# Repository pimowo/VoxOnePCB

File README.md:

# VoxOnePCB — VoxOne_M1

Repozytorium projektu płytki **VoxOne_M1** (KiCad 10.0.4). Oddzielone od firmware VoxOne/VoxOneBT.

## Dokumentacja

- [TODO.md](TODO.md) — **kanoniczny notatnik** zadań, zatwierdzonych wytycznych, blokad i historii.
- [AGENTS.md](AGENTS.md) — zasady pracy lokalnego Codexa.
- [docs/IMPORT_KICAD.md](docs/IMPORT_KICAD.md) — bezpieczne przeniesienie źródeł projektu na GitHub.

## Zatwierdzone wymagania PCB

- Laminat maksymalnie **100 × 100 mm**; cztery otwory M3.
- **2 warstwy miedzi**, ścieżki TOP i BOTTOM.
- **Wszystkie elementy montowane wyłącznie od góry (TOP)** — SMD i THT, moduły, goldpiny, zworki.
- MAIN po lewej, DAC w górnej prawej części, BT po prawej, RTC blisko środka, dolna strefa uporządkowanych złączy: **wytyczna koncepcyjna**, wymagająca mechanicznej kontroli.
- Moduły MAIN/BT/DAC/RTC wymienne.

## Stan projektu

Ostatnia importowana rewizja: **FOOTPRINT-2 + PCB-PREVIEW-1**. Według raportu Codexa: ERC 0 błędów i 0 ostrzeżeń; wstępne PCB 100 × 100 mm bez trasowania. **Rozmieszczenie PREVIEW-1 zostało odrzucone.** Nie tworzyć Gerberów ani nie trasować tej wersji. Geometrie trzech dużych modułów są referencyjne (PROVISIONAL), niepotwierdzone na fizycznych egzemplarzach.

**Źródła projektu KiCad i biblioteki są już opublikowane w repozytorium**, od bazowego commita [`8d90e6d`](https://github.com/pimowo/VoxOnePCB/commit/8d90e6df444f770a445944372fa62b5ebb39af9). W repo znajdują się pliki `.kicad_pro`, `.kicad_sch`, `.kicad_pcb`, projektowe biblioteki footprintów/symboli i wybrane modele 3D. Z publikacji wyłączono modele `YD-ESP32-S3.step` i `PCM5102-I2S.step` do dalszej weryfikacji praw. Po imporcie projekt otwarto w KiCad 3D, ale **należy ponownie wykonać ERC/DRC/netlist na czystym klonie**. Wersja jest PROVISIONAL i nie jest zatwierdzona do produkcji.

## Dostęp i prawa

Repozytorium jest **publiczne**. Nie publikować kluczy, haseł, danych prywatnych, ani obcych modeli 3D/bibliotek bez zgodnej licencji. **Licencja własnego projektu nie została jeszcze wybrana** — nie dodawać `LICENSE` automatycznie.

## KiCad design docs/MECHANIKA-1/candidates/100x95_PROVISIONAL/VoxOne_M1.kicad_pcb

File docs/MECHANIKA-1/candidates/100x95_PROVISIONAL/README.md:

# Kandydat analityczny 100×95 mm — PROVISIONAL

Otwórz `VoxOne_M1.kicad_pro` w tym katalogu. To niezależna kopia do analizy, nie zmiana głównego PCB. Schemat A2 i konfiguracja są bajtowo identyczne ze źródłem. Footprinty/symbole/modele są współdzielone przez ścieżki względne do głównego katalogu repozytorium; przenoś cały klon, nie sam ten podkatalog. Pełny model MAIN działa tylko lokalnie i nie jest publikowany. Nie ma pełnych brył BT/DAC/RTC/F101. Braki są jawne w podglądzie3D.

77 TOP,4M3,0tras/via/pours,ERC0/0,DRC173niepołączenia i0innych naruszeń. Nie jest to DRC PASS ani finalny layout. Wygoda złączy, tolerancje iZ są niepotwierdzone; patrz raporty dwa katalogi wyżej. Nie trasować ani nie produkować bez nowego polecenia użytkownika.

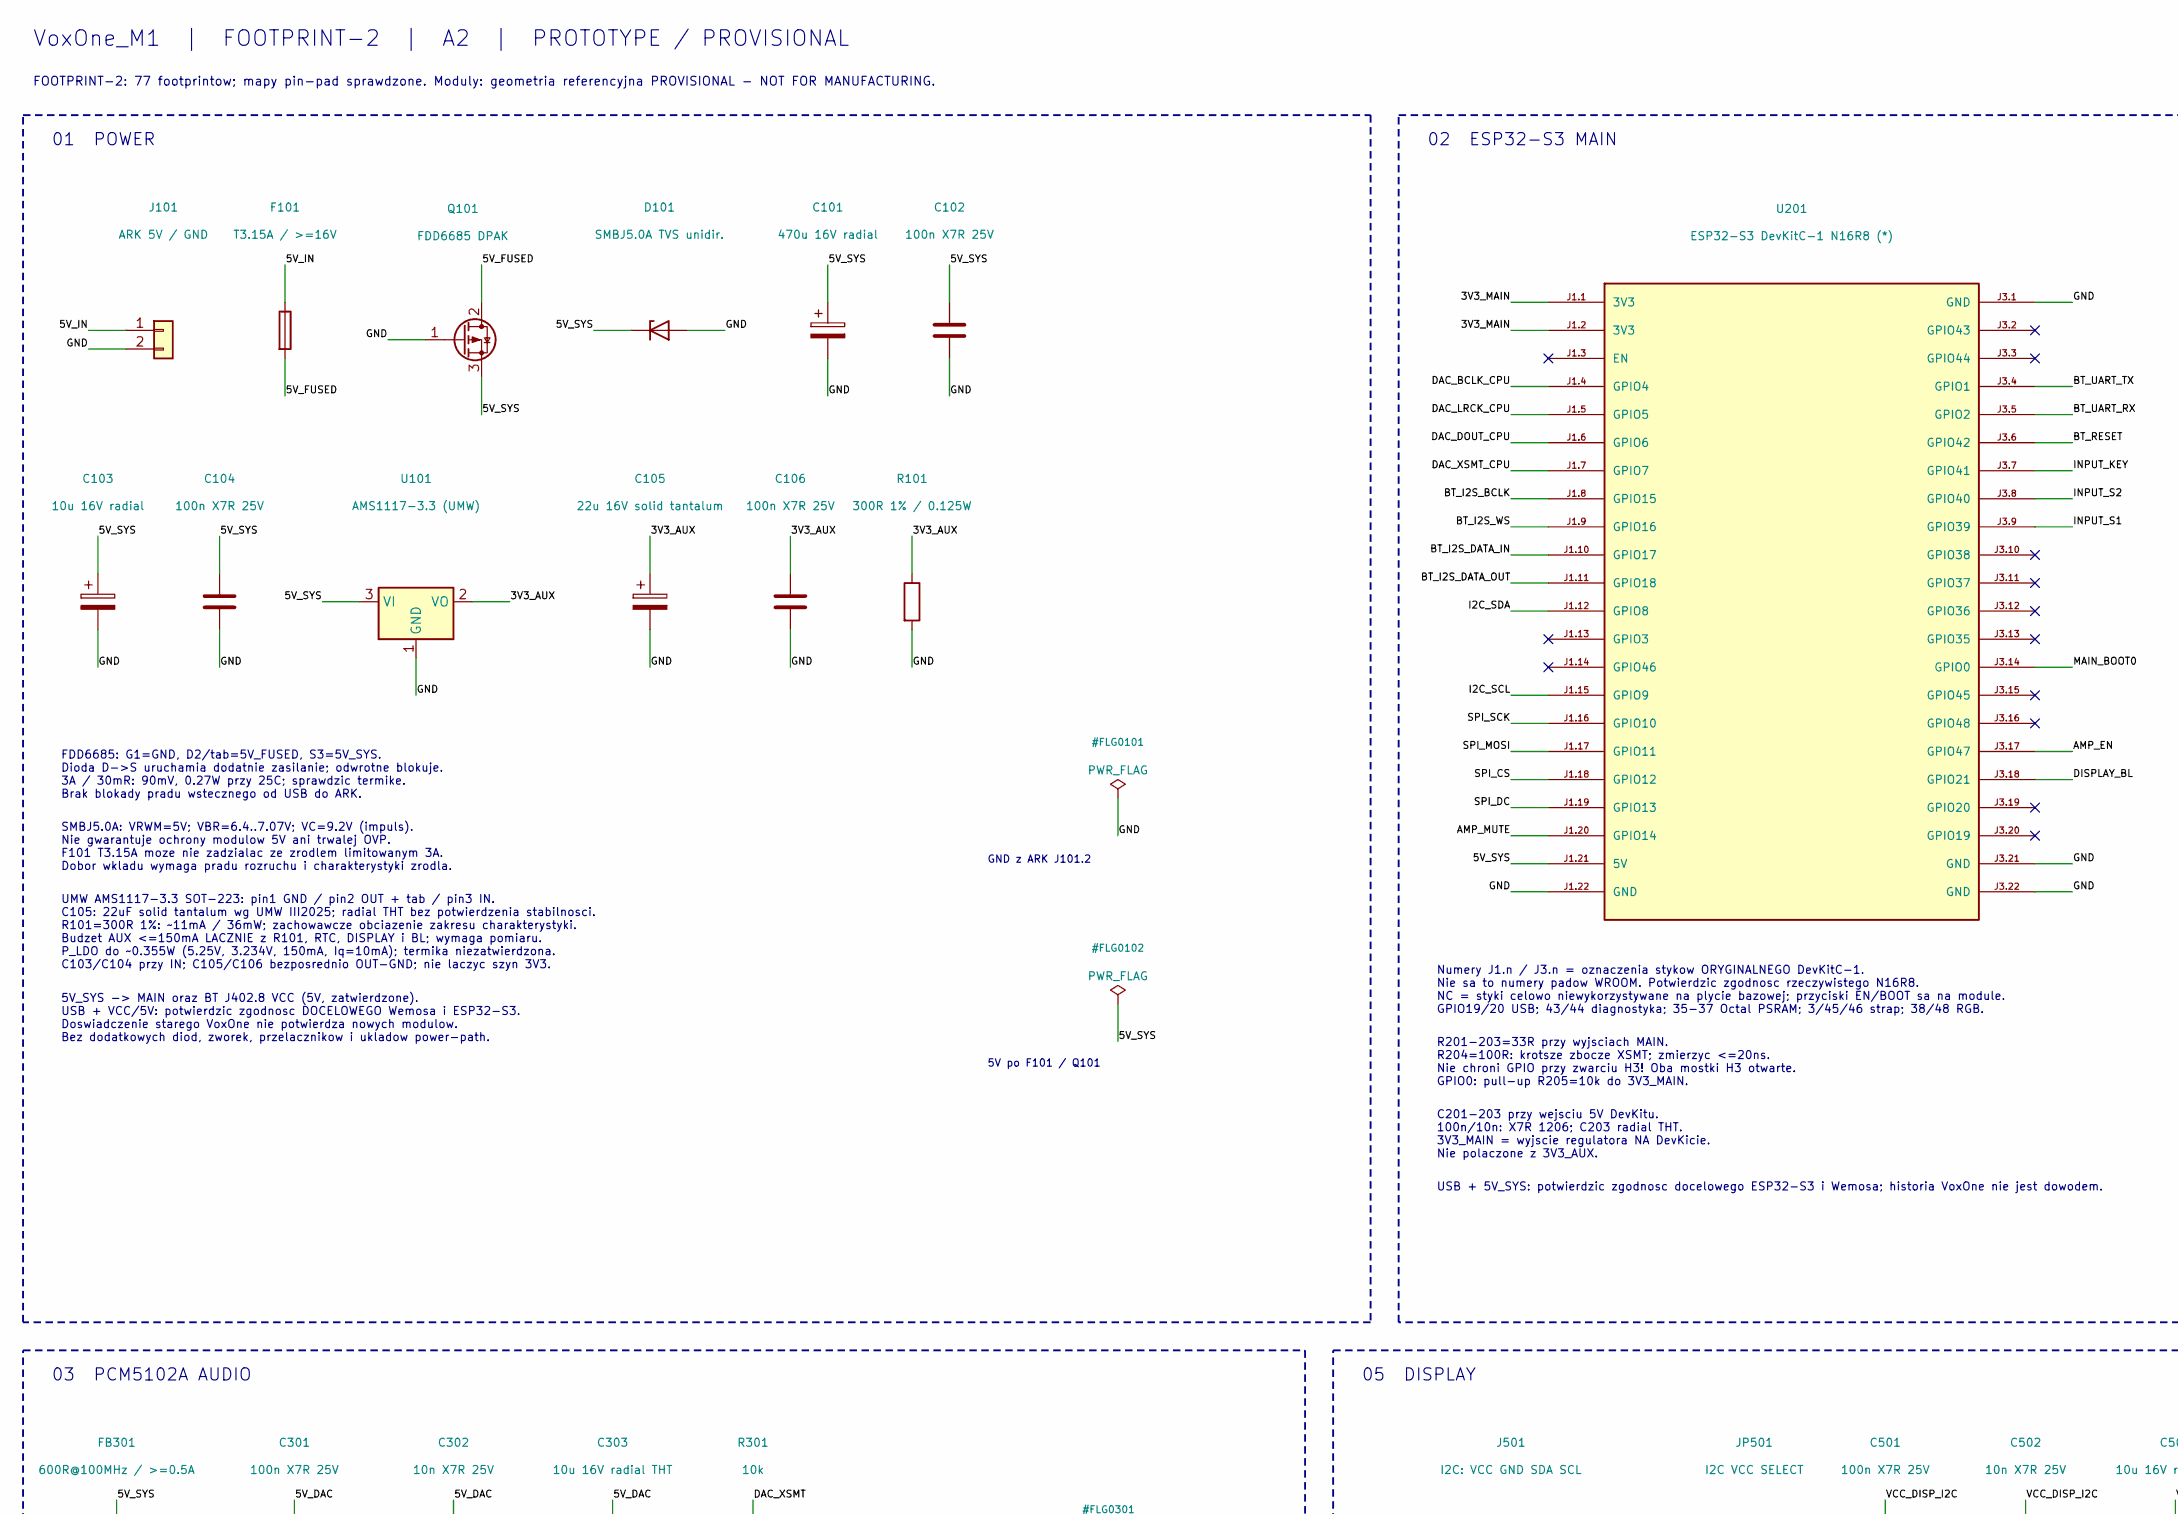
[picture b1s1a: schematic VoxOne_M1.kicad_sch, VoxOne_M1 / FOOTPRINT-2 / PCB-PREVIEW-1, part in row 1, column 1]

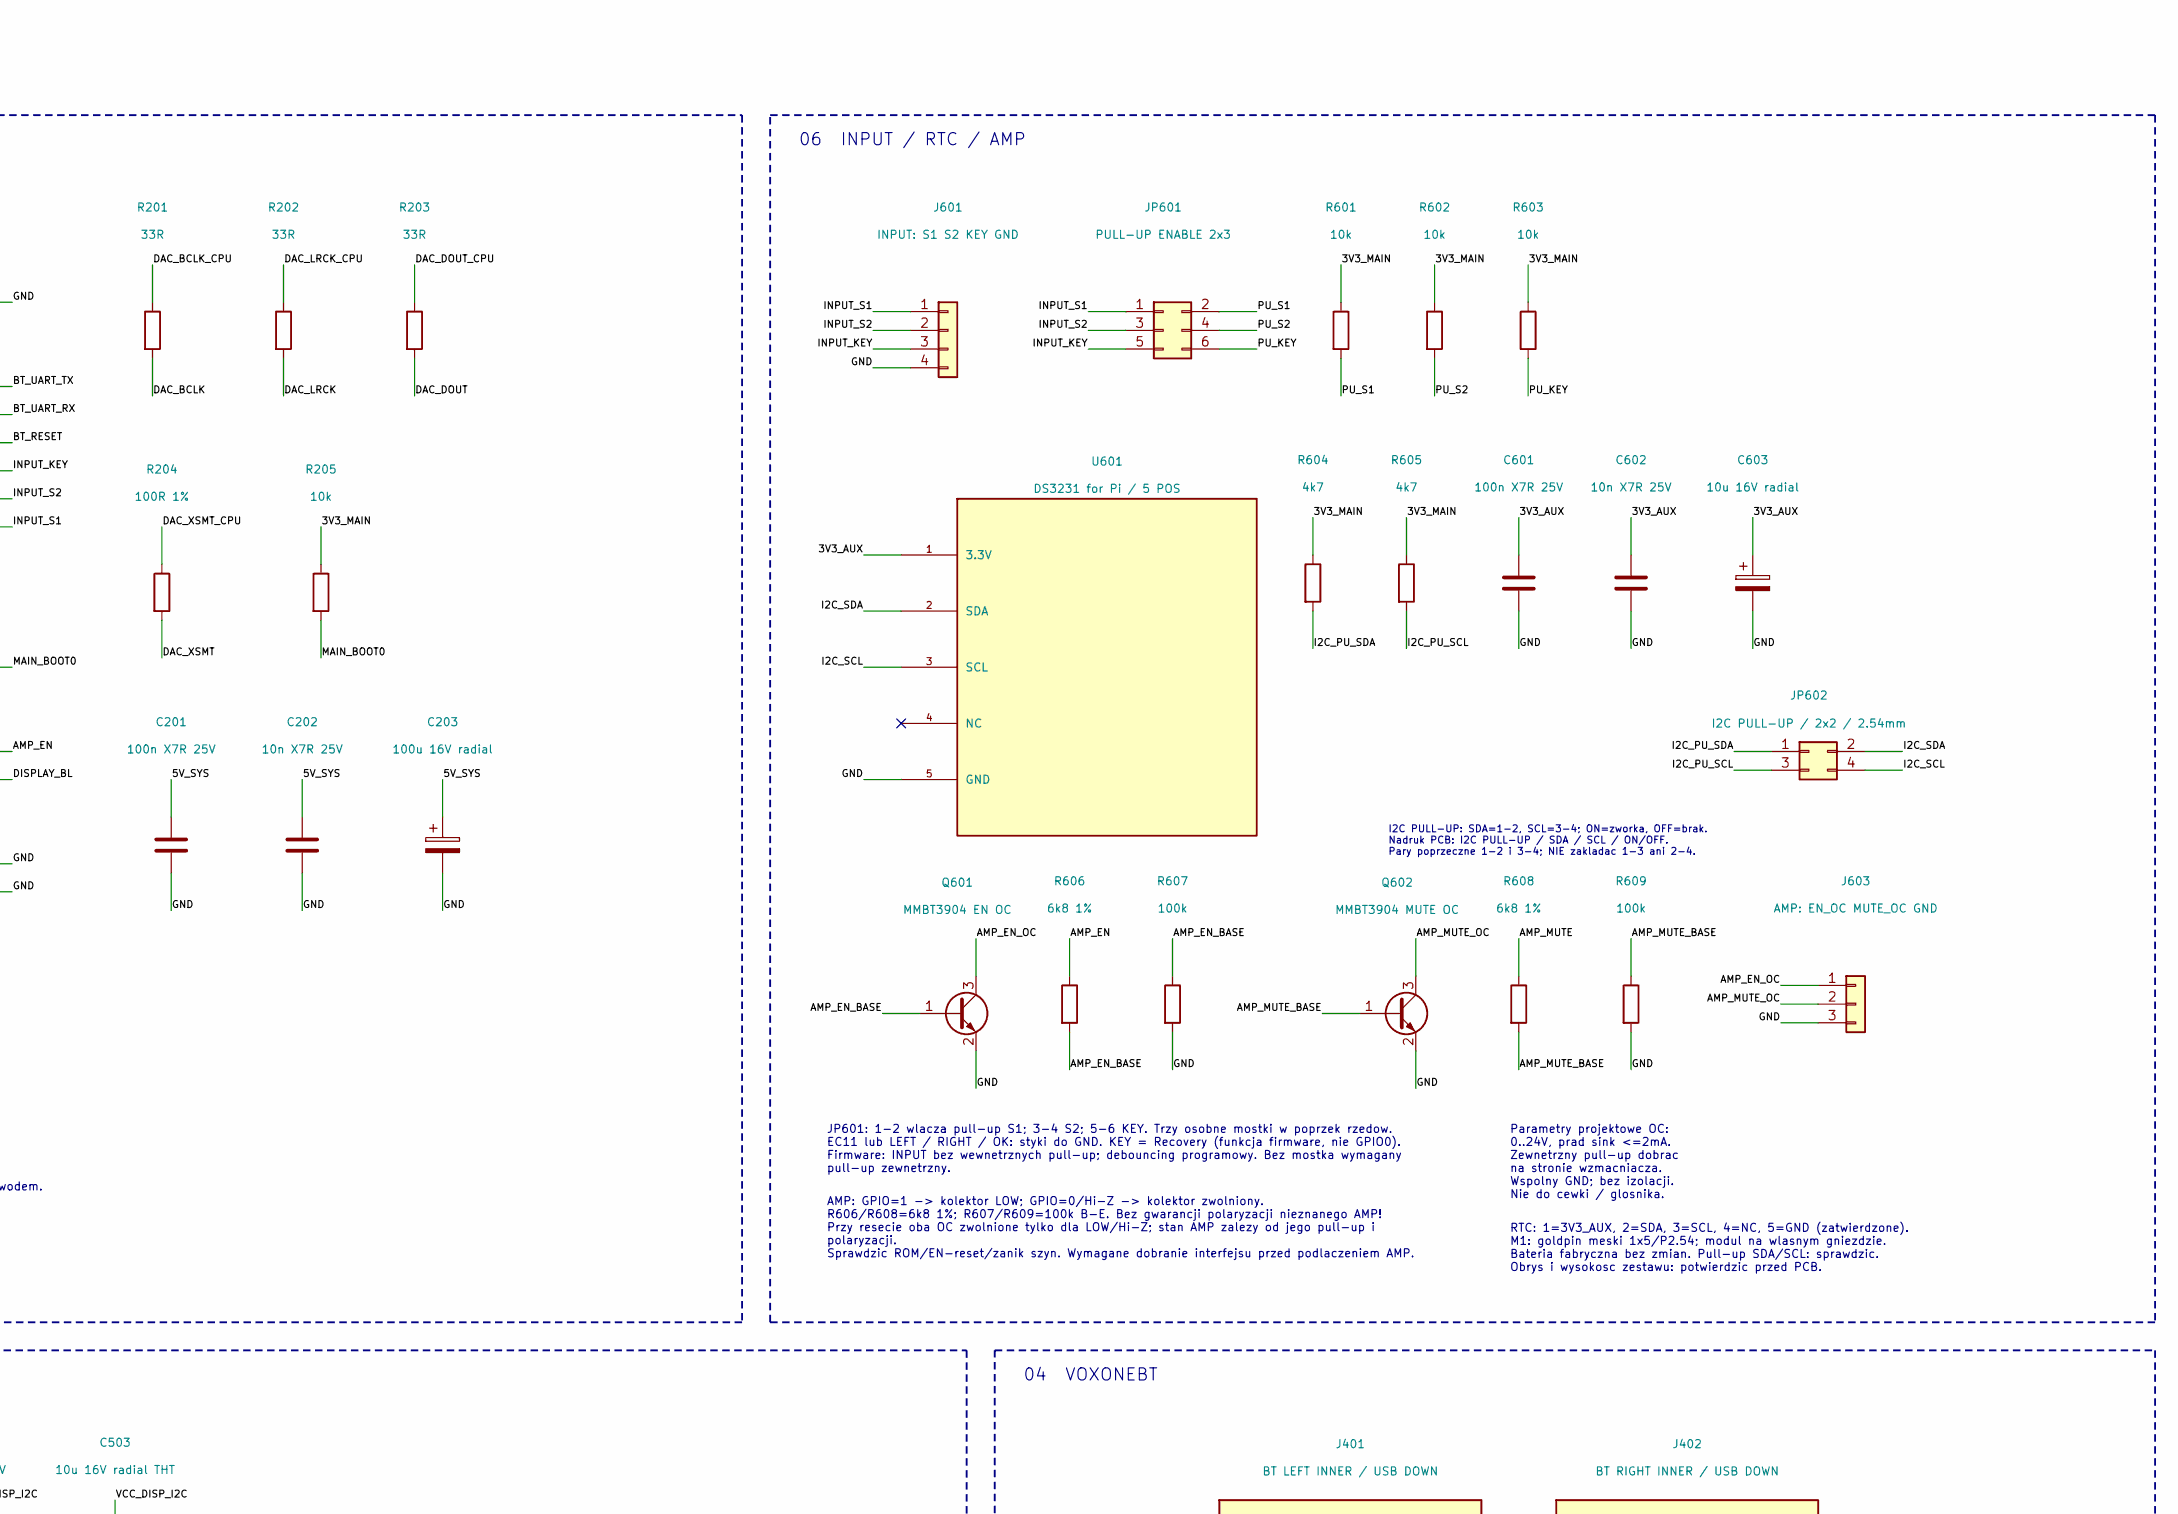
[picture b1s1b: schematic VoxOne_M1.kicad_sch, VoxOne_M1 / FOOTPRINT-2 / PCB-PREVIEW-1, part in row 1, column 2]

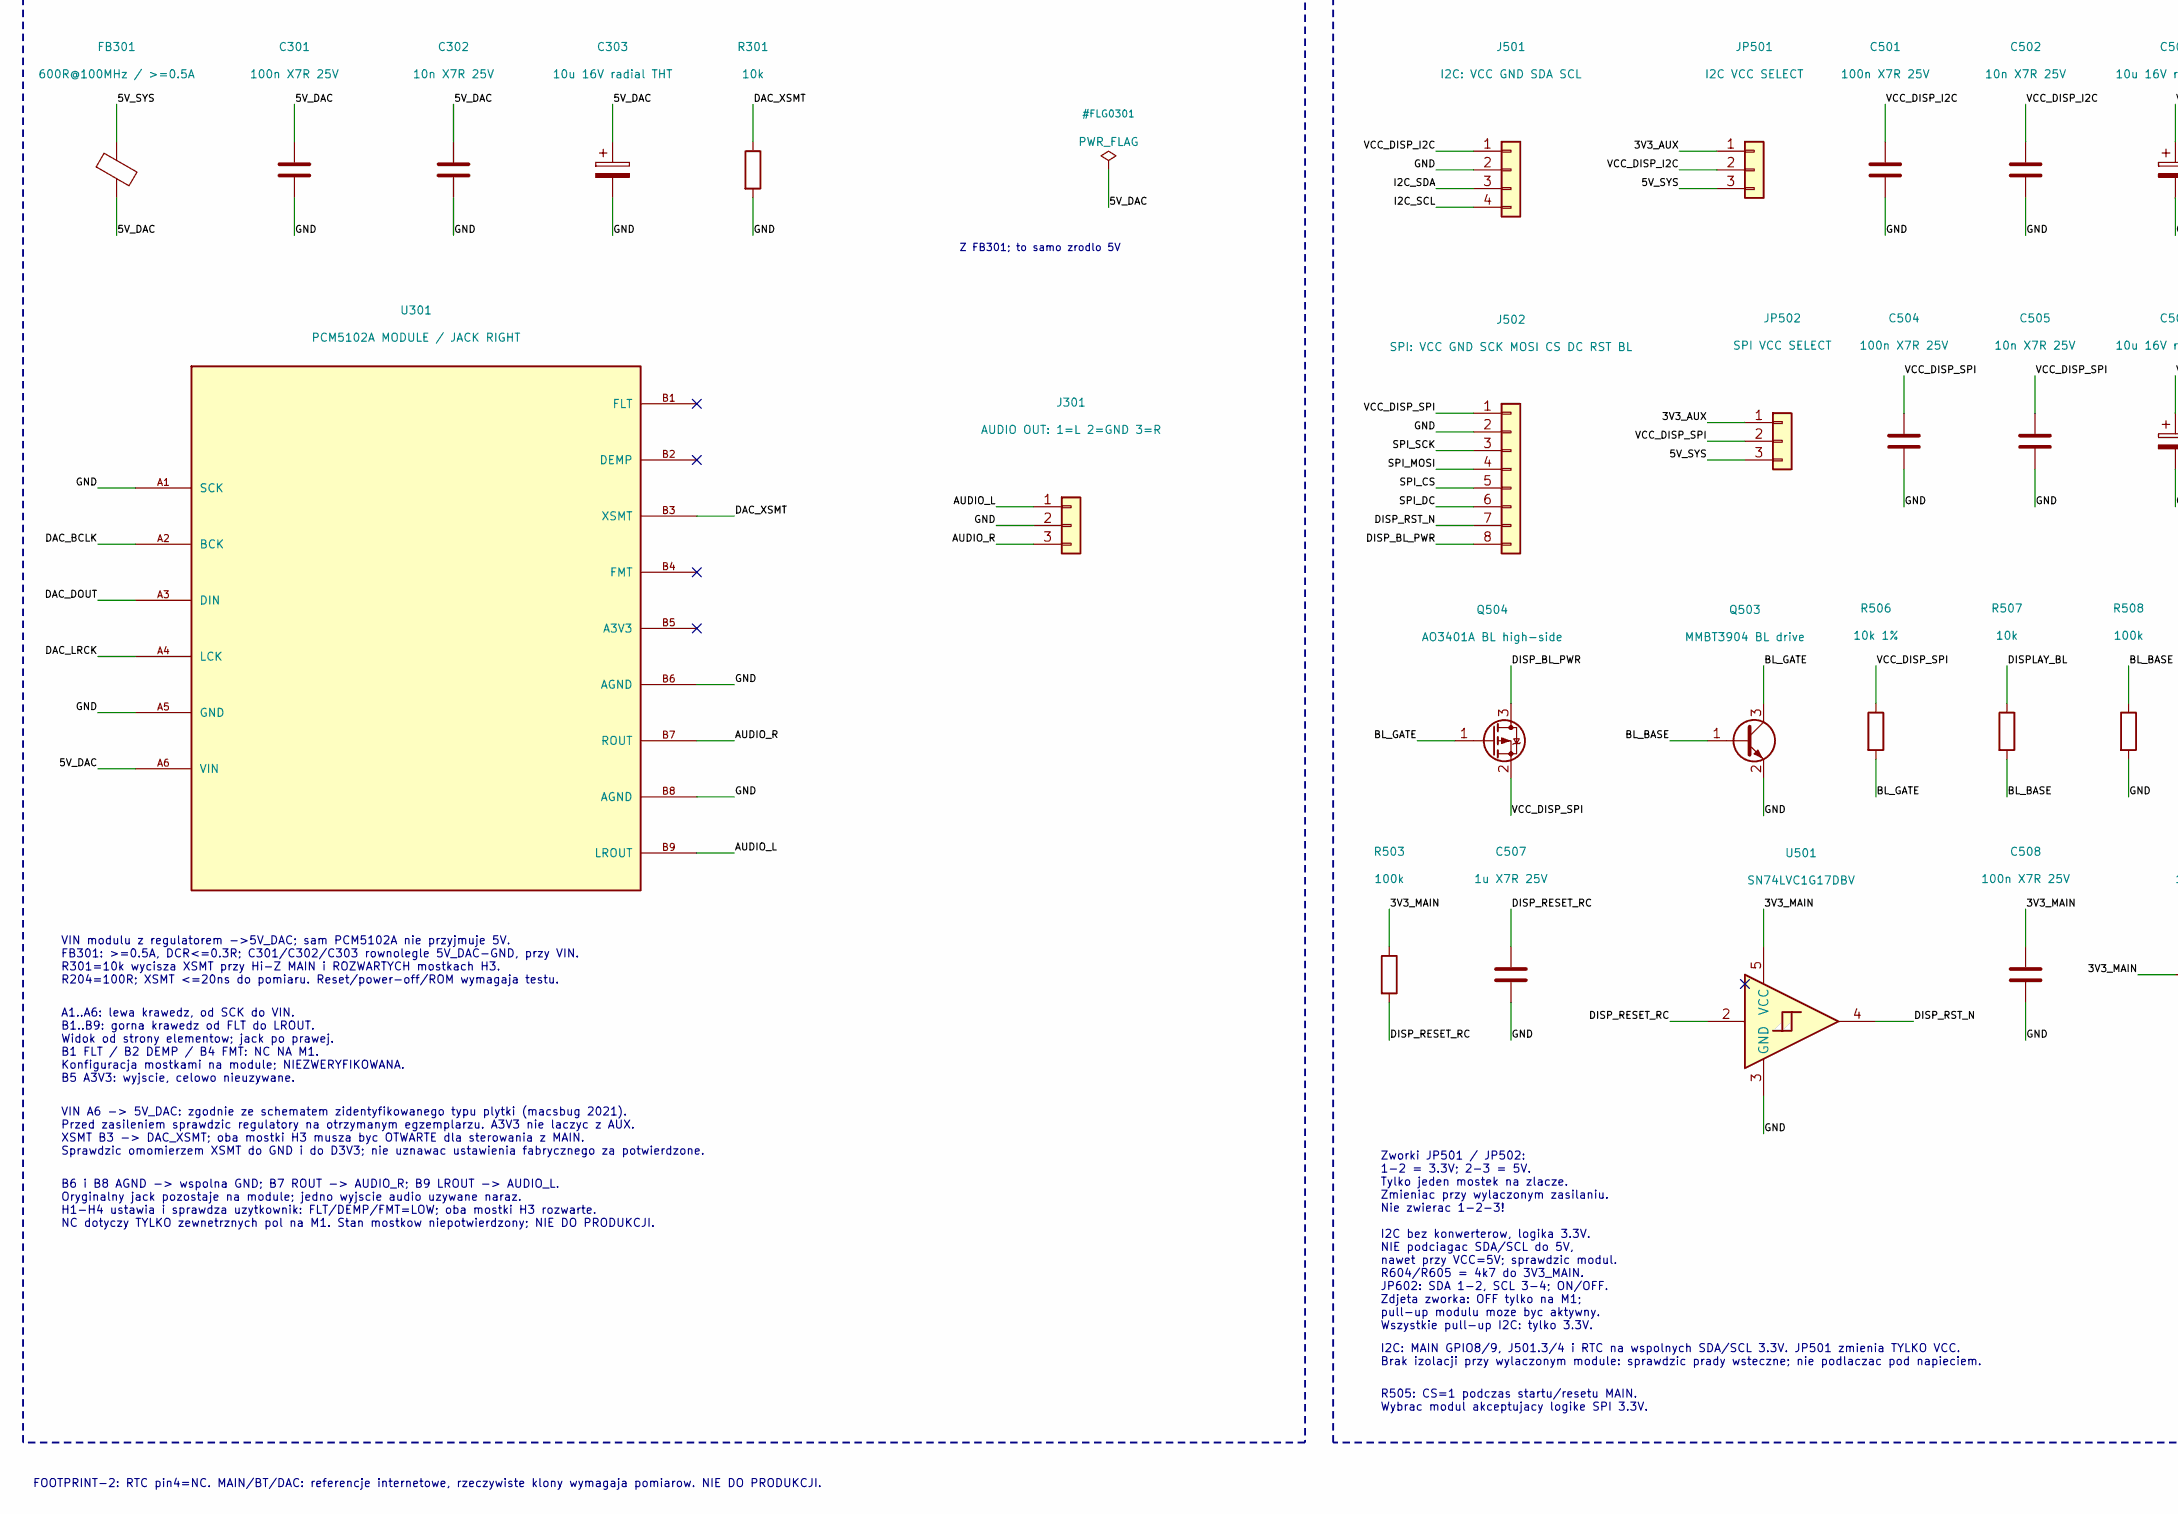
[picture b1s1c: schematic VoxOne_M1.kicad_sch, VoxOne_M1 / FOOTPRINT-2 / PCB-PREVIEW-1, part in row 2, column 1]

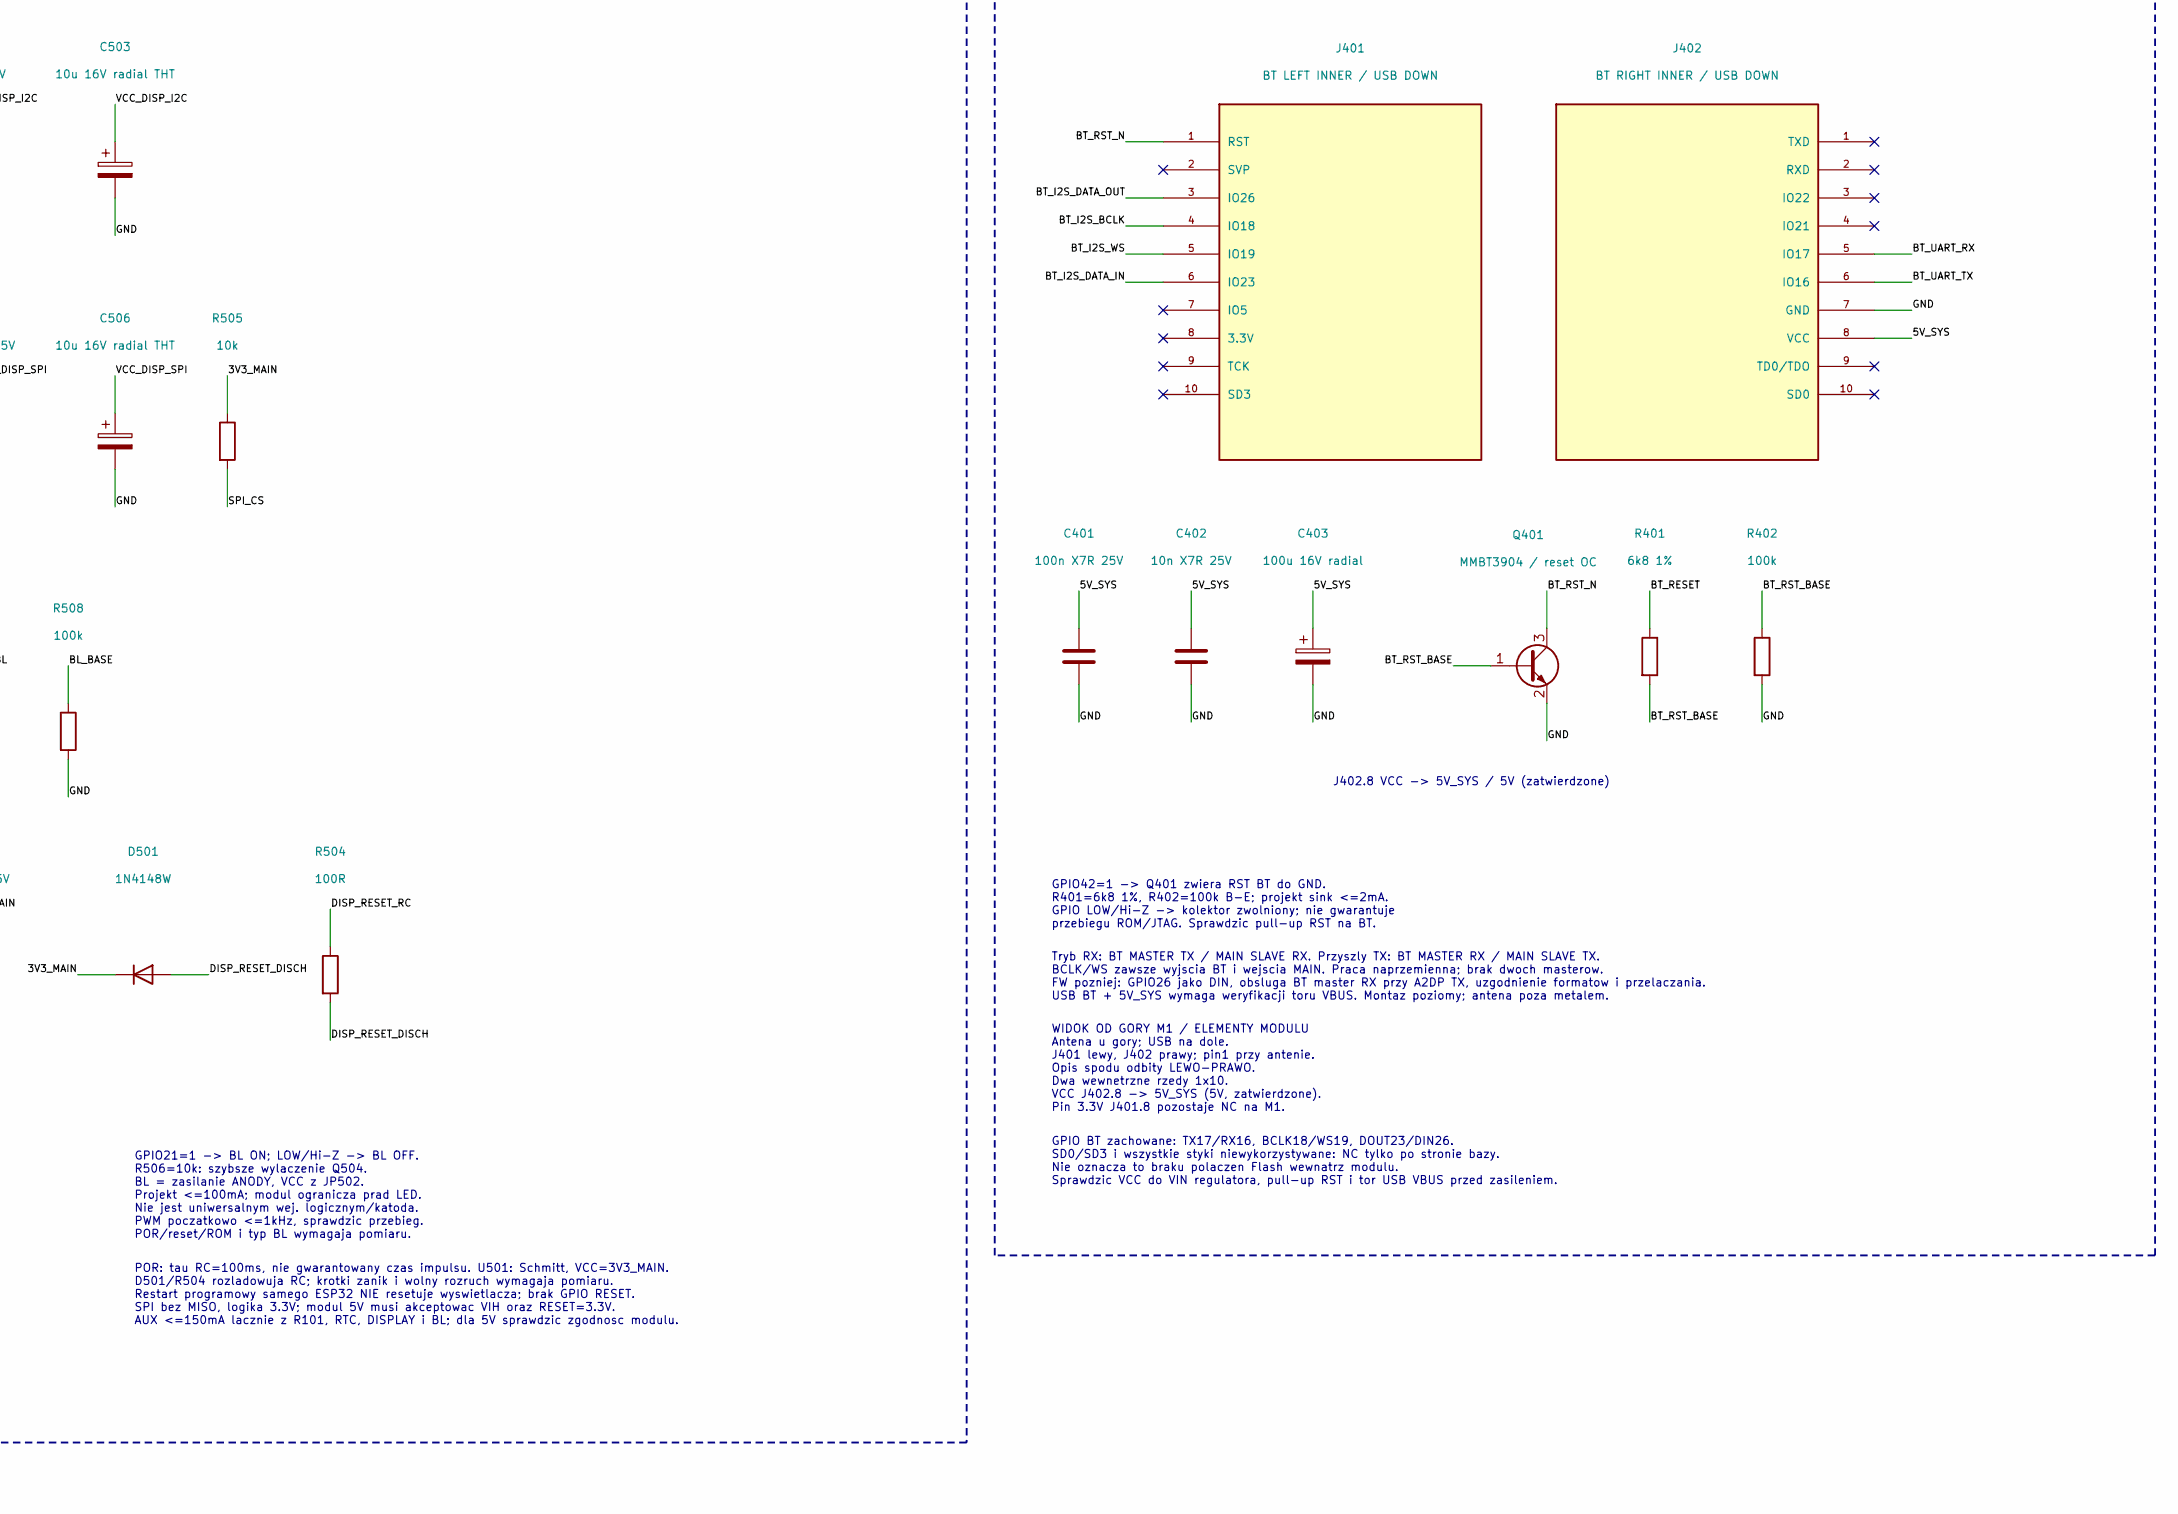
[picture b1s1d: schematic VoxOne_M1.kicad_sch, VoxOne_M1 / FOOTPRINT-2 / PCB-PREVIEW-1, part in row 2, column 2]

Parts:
C101: 470u 16V radial; CP_Radial_D10.0mm_P5.00mm
C102, C104, C106, C201, C301, C401, C501, C504, C508, C601: 100n X7R 25V; C_1206_3216Metric
C103, C603: 10u 16V radial; CP_Radial_D5.0mm_P2.00mm
C105: 22u 16V solid tantalum; CP_EIA-7343-31_Kemet-D_HandSolder
C202, C302, C402, C502, C505, C602: 10n X7R 25V; C_1206_3216Metric
C203, C403: 100u 16V radial; CP_Radial_D5.0mm_P2.00mm
C303, C503, C506: 10u 16V radial THT; CP_Radial_D5.0mm_P2.00mm
C507: 1u X7R 25V; C_1206_3216Metric
D101: SMBJ5.0A TVS unidir.; D_SMB
D501: 1N4148W; D_SOD-123
F101: T3.15A / >=16V; Fuse_Littelfuse_372_D8.50mm
FB301: 600R@100MHz / >=0.5A; L_1206_3216Metric
J101: ARK 5V / GND; TerminalBlock_Phoenix_MKDS-1,5-2-5.08_1x02_P5.08mm_Horizont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
J301: AUDIO OUT: 1=L 2=GND 3=R; PinHeader_1x03_P2.54mm_Vertical
J401: BT LEFT INNER / USB DOWN; Socket_Wemos_INNER_LEFT_1x10_P2.54mm_PROVISIONAL
J402: BT RIGHT INNER / USB DOWN; Socket_Wemos_INNER_RIGHT_1x10_P2.54mm_PROVISIONAL
J501: I2C: VCC GND SDA SCL; PinHeader_1x04_P2.54mm_Vertical
J502: SPI: VCC GND SCK MOSI CS DC RST BL; PinHeader_1x08_P2.54mm_Vertical
J601: INPUT: S1 S2 KEY GND; PinHeader_1x04_P2.54mm_Vertical
J603: AMP: EN_OC MUTE_OC GND; PinHeader_1x03_P2.54mm_Vertical
JP501: I2C VCC SELECT; PinHeader_1x03_P2.54mm_Vertical
JP502: SPI VCC SELECT; PinHeader_1x03_P2.54mm_Vertical
JP601: PULL-UP ENABLE 2x3; PinHeader_2x03_P2.54mm_Vertical
JP602: I2C PULL-UP / 2x2 / 2.54mm; PinHeader_2x02_P2.54mm_Vertical
Q101: FDD6685 DPAK; TO-252_FDD6685_369AS_HandSolder
Q401: MMBT3904 / reset OC; SOT-23
Q503: MMBT3904 BL drive; SOT-23
Q504: AO3401A BL high-side; SOT-23
Q601: MMBT3904 EN OC; SOT-23
Q602: MMBT3904 MUTE OC; SOT-23
R101: 300R 1% / 0.125W; R_1206_3216Metric
R201, R202, R203: 33R; R_1206_3216Metric
R204: 100R 1%; R_1206_3216Metric
R205, R301, R505, R507, R601, R602, R603: 10k; R_1206_3216Metric
R401, R606, R608: 6k8 1%; R_1206_3216Metric
R402, R503, R508, R607, R609: 100k; R_1206_3216Metric
R504: 100R; R_1206_3216Metric
R506: 10k 1%; R_1206_3216Metric
R604, R605: 4k7; R_1206_3216Metric
U101: AMS1117-3.3 (UMW); SOT-223-3_TabPin2
U201: ESP32-S3 DevKitC-1 N16R8 (*); Socket_YD_ESP32S3_44_PROVISIONAL
U301: PCM5102A MODULE / JACK RIGHT; Socket_GY_PCM5102A_6_9_PROVISIONAL
U501: SN74LVC1G17DBV; SOT-23-5
U601: DS3231 for Pi / 5 POS; PinHeader_1x05_P2.54mm_Vertical

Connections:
/3V3_AUX: C105.1, C106.1, C601.1, C602.1, C603.1, JP501.1, JP502.1, R101.1, U101.2 (VO), U601.1 (3.3V)
/3V3_MAIN: C508.1, D501.1 (K), R205.1, R503.1, R505.1, R601.1, R602.1, R603.1, R604.1, R605.1, U201.J1.1 (3V3), U201.J1.2 (3V3), U501.5 (VCC)
/5V_DAC: C301.1, C302.1, C303.1, FB301.2, U301.A6 (VIN)
/5V_FUSED: F101.2, Q101.2 (D)
/5V_IN: F101.1, J101.1
/5V_SYS: C101.1, C102.1, C103.1, C104.1, C201.1, C202.1, C203.1, C401.1, C402.1, C403.1, D101.1 (K), FB301.1, J402.8 (VCC), JP501.3, JP502.3, Q101.3 (S), U101.3 (VI), U201.J1.21 (5V)
/AMP_EN: R606.1, U201.J3.17 (GPIO47)
/AMP_EN_BASE: Q601.1 (B), R606.2, R607.1
/AMP_EN_OC: J603.1, Q601.3 (C)
/AMP_MUTE: R608.1, U201.J1.20 (GPIO14)
/AMP_MUTE_BASE: Q602.1 (B), R608.2, R609.1
/AMP_MUTE_OC: J603.2, Q602.3 (C)
/AUDIO_L: J301.1, U301.B9 (LROUT)
/AUDIO_R: J301.3, U301.B7 (ROUT)
/BL_BASE: Q503.1 (B), R507.2, R508.1
/BL_GATE: Q503.3 (C), Q504.1 (G), R506.2
/BT_I2S_BCLK: J401.4 (IO18), U201.J1.8 (GPIO15)
/BT_I2S_DATA_IN: J401.6 (IO23), U201.J1.10 (GPIO17)
/BT_I2S_DATA_OUT: J401.3 (IO26), U201.J1.11 (GPIO18)
/BT_I2S_WS: J401.5 (IO19), U201.J1.9 (GPIO16)
/BT_RESET: R401.1, U201.J3.6 (GPIO42)
/BT_RST_BASE: Q401.1 (B), R401.2, R402.1
/BT_RST_N: J401.1 (RST), Q401.3 (C)
/BT_UART_RX: J402.5 (IO17), U201.J3.5 (GPIO2)
/BT_UART_TX: J402.6 (IO16), U201.J3.4 (GPIO1)
/DAC_BCLK: R201.2, U301.A2 (BCK)
/DAC_BCLK_CPU: R201.1, U201.J1.4 (GPIO4)
/DAC_DOUT: R203.2, U301.A3 (DIN)
/DAC_DOUT_CPU: R203.1, U201.J1.6 (GPIO6)
/DAC_LRCK: R202.2, U301.A4 (LCK)
/DAC_LRCK_CPU: R202.1, U201.J1.5 (GPIO5)
/DAC_XSMT: R204.2, R301.1, U301.B3 (XSMT)
/DAC_XSMT_CPU: R204.1, U201.J1.7 (GPIO7)
/DISPLAY_BL: R507.1, U201.J3.18 (GPIO21)
/DISP_BL_PWR: J502.8, Q504.3 (D)
/DISP_RESET_DISCH: D501.2 (A), R504.2
/DISP_RESET_RC: C507.1, R503.2, R504.1, U501.2
/DISP_RST_N: J502.7, U501.4
/GND: C101.2, C102.2, C103.2, C104.2, C105.2, C106.2, C201.2, C202.2, C203.2, C301.2, C302.2, C303.2, C401.2, C402.2, C403.2, C501.2, C502.2, C503.2, C504.2, C505.2, C506.2, C507.2, C508.2, C601.2, C602.2, C603.2, D101.2 (A), J101.2, J301.2, J402.7 (GND), J501.2, J502.2, J601.4, J603.3, Q101.1 (G), Q401.2 (E), Q503.2 (E), Q601.2 (E), Q602.2 (E), R101.2, R301.2, R402.2, R508.2, R607.2, R609.2, U101.1 (GND), U201.J1.22 (GND), U201.J3.1 (GND), U201.J3.21 (GND), U201.J3.22 (GND), U301.A1 (SCK), U301.A5 (GND), U301.B6 (AGND), U301.B8 (AGND), U501.3 (GND), U601.5 (GND)
/I2C_PU_SCL: JP602.3, R605.2
/I2C_PU_SDA: JP602.1, R604.2
/I2C_SCL: J501.4, JP602.4, U201.J1.15 (GPIO9), U601.3 (SCL)
/I2C_SDA: J501.3, JP602.2, U201.J1.12 (GPIO8), U601.2 (SDA)
/INPUT_KEY: J601.3, JP601.5, U201.J3.7 (GPIO41)
/INPUT_S1: J601.1, JP601.1, U201.J3.9 (GPIO39)
/INPUT_S2: J601.2, JP601.3, U201.J3.8 (GPIO40)
/MAIN_BOOT0: R205.2, U201.J3.14 (GPIO0)
/PU_KEY: JP601.6, R603.2
/PU_S1: JP601.2, R601.2
/PU_S2: JP601.4, R602.2
/SPI_CS: J502.5, R505.2, U201.J1.18 (GPIO12)
/SPI_DC: J502.6, U201.J1.19 (GPIO13)
/SPI_MOSI: J502.4, U201.J1.17 (GPIO11)
/SPI_SCK: J502.3, U201.J1.16 (GPIO10)
/VCC_DISP_I2C: C501.1, C502.1, C503.1, J501.1, JP501.2
/VCC_DISP_SPI: C504.1, C505.1, C506.1, J502.1, JP502.2, Q504.2 (S), R506.1

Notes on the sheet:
01 POWER
02 ESP32-S3 MAIN
06 INPUT / RTC / AMP
03 PCM5102A AUDIO
05 DISPLAY
04 VOXONEBT
FDD6685: G1=GND, D2/tab=5V_FUSED, S3=5V_SYS. Dioda D->S uruchamia dodatnie zasilanie; odwrotne blokuje. 3A / 30mR: 90mV, 0.27W przy 25C; sprawdzic termike. Brak blokady pradu wstecznego od USB do ARK.
SMBJ5.0A: VRWM=5V; VBR=6.4..7.07V; VC=9.2V (impuls). Nie gwarantuje ochrony modulow 5V ani trwalej OVP. F101 T3.15A moze nie zadzialac ze zrodlem limitowanym 3A. Dobor wkladu wymaga pradu rozruchu i charakterystyki zrodla.
UMW AMS1117-3.3 SOT-223: pin1 GND / pin2 OUT + tab / pin3 IN. C105: 22uF solid tantalum wg UMW III2025; radial THT bez potwierdzenia stabilnosci. R101=300R 1%: ~11mA / 36mW; zachowawcze obciazenie zakresu charakterystyki. Budzet AUX <=150mA LACZNIE z R101, RTC, DISPLAY i BL; wymaga pomiaru. P_LDO d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
5V_SYS -> MAIN oraz BT J402.8 VCC (5V, zatwierdzone). USB + VCC/5V: potwierdzic zgodnosc DOCELOWEGO Wemosa i ESP32-S3. Doswiadczenie starego VoxOne nie potwierdza nowych modulow. Bez dodatkowych diod, zworek, przelacznikow i ukladow power-path.
Numery J1.n / J3.n = oznaczenia stykow ORYGINALNEGO DevKitC-1. Nie sa to numery padow WROOM. Potwierdzic zgodnosc rzeczywistego N16R8. NC = styki celowo niewykorzystywane na plycie bazowej; przyciski EN/BOOT sa na module. GPIO19/20 USB; 43/44 diagnostyka; 35-37 Octal PSRAM; 3/45/46 strap; 38/48 RGB.
R201-203=33R przy wyjsciach MAIN. R204=100R: krotsze zbocze XSMT; zmierzyc <=20ns. Nie chroni GPIO przy zwarciu H3! Oba mostki H3 otwarte. GPIO0: pull-up R205=10k do 3V3_MAIN.
C201-203 przy wejsciu 5V DevKitu. 100n/10n: X7R 1206; C203 radial THT. 3V3_MAIN = wyjscie regulatora NA DevKicie. Nie polaczone z 3V3_AUX.
USB + 5V_SYS: potwierdzic zgodnosc docelowego ESP32-S3 i Wemosa; historia VoxOne nie jest dowodem.
JP601: 1-2 wlacza pull-up S1; 3-4 S2; 5-6 KEY. Trzy osobne mostki w poprzek rzedow. EC11 lub LEFT / RIGHT / OK: styki do GND. KEY = Recovery (funkcja firmware, nie GPIO0). Firmware: INPUT bez wewnetrznych pull-up; debouncing programowy. Bez mostka wymagany pull-up zewnetrzny.
AMP: GPIO=1 -> kolektor LOW; GPIO=0/Hi-Z -> kolektor zwolniony. R606/R608=6k8 1%; R607/R609=100k B-E. Bez gwarancji polaryzacji nieznanego AMP! Przy resecie oba OC zwolnione tylko dla LOW/Hi-Z; stan AMP zalezy od jego pull-up i polaryzacji. Sprawdzic ROM/EN-reset/zanik szyn. Wymagane dobranie inter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
Parametry projektowe OC: 0..24V, prad sink <=2mA. Zewnetrzny pull-up dobrac na stronie wzmacniacza. Wspolny GND; bez izolacji. Nie do cewki / glosnika.
RTC: 1=3V3_AUX, 2=SDA, 3=SCL, 4=NC, 5=GND (zatwierdzone). M1: goldpin meski 1x5/P2.54; modul na wlasnym gniezdzie. Bateria fabryczna bez zmian. Pull-up SDA/SCL: sprawdzic. Obrys i wysokosc zestawu: potwierdzic przed PCB.
VIN modulu z regulatorem ->5V_DAC; sam PCM5102A nie przyjmuje 5V. FB301: >=0.5A, DCR<=0.3R; C301/C302/C303 rownolegle 5V_DAC-GND, przy VIN. R301=10k wycisza XSMT przy Hi-Z MAIN i ROZWARTYCH mostkach H3. R204=100R; XSMT <=20ns do pomiaru. Reset/power-off/ROM wymagaja testu.
A1..A6: lewa krawedz, od SCK do VIN. B1..B9: gorna krawedz od FLT do LROUT. Widok od strony elementow; jack po prawej. B1 FLT / B2 DEMP / B4 FMT: NC NA M1. Konfiguracja mostkami na module; NIEZWERYFIKOWANA. B5 A3V3: wyjscie, celowo nieuzywane.
VIN A6 -> 5V_DAC: zgodnie ze schematem zidentyfikowanego typu plytki (macsbug 2021). Przed zasileniem sprawdzic regulatory na otrzymanym egzemplarzu. A3V3 nie laczyc z AUX. XSMT B3 -> DAC_XSMT; oba mostki H3 musza byc OTWARTE dla sterowania z MAIN. Sprawdzic omomierzem XSMT do GND i do D3V3; nie uz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
B6 i B8 AGND -> wspolna GND; B7 ROUT -> AUDIO_R; B9 LROUT -> AUDIO_L. Oryginalny jack pozostaje na module; jedno wyjscie audio uzywane naraz. H1-H4 ustawia i sprawdza uzytkownik: FLT/DEMP/FMT=LOW; oba mostki H3 rozwarte. NC dotyczy TYLKO zewnetrznych pol na M1. Stan mostkow niepotwierdzony; NIE DO 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
Zworki JP501 / JP502: 1-2 = 3.3V; 2-3 = 5V. Tylko jeden mostek na zlacze. Zmieniac przy wylaczonym zasilaniu. Nie zwierac 1-2-3! I2C bez konwerterow, logika 3.3V. NIE podciagac SDA/SCL do 5V, nawet przy VCC=5V; sprawdzic modul. R604/R605 = 4k7 do 3V3_MAIN. JP602: SDA 1-2, SCL 3-4; ON/OFF. Zdjeta zw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
I2C: MAIN GPIO8/9, J501.3/4 i RTC na wspolnych SDA/SCL 3.3V. JP501 zmienia TYLKO VCC. Brak izolacji przy wylaczonym module: sprawdzic prady wsteczne; nie podlaczac pod napieciem.
R505: CS=1 podczas startu/resetu MAIN. Wybrac modul akceptujacy logike SPI 3.3V.
GPIO21=1 -> BL ON; LOW/Hi-Z -> BL OFF. R506=10k: szybsze wylaczenie Q504. BL = zasilanie ANODY, VCC z JP502. Projekt <=100mA; modul ogranicza prad LED. Nie jest uniwersalnym wej. logicznym/katoda. PWM poczatkowo <=1kHz, sprawdzic przebieg. POR/reset/ROM i typ BL wymagaja pomiaru.
POR: tau RC=100ms, nie gwarantowany czas impulsu. U501: Schmitt, VCC=3V3_MAIN. D501/R504 rozladowuja RC; krotki zanik i wolny rozruch wymagaja pomiaru. Restart programowy samego ESP32 NIE resetuje wyswietlacza; brak GPIO RESET. SPI bez MISO, logika 3.3V; modul 5V musi akceptowac VIH oraz RESET=3.3V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
J402.8 VCC -> 5V_SYS / 5V (zatwierdzone)
GPIO42=1 -> Q401 zwiera RST BT do GND. R401=6k8 1%, R402=100k B-E; projekt sink <=2mA. GPIO LOW/Hi-Z -> kolektor zwolniony; nie gwarantuje przebiegu ROM/JTAG. Sprawdzic pull-up RST na BT.
Tryb RX: BT MASTER TX / MAIN SLAVE RX. Przyszly TX: BT MASTER RX / MAIN SLAVE TX. BCLK/WS zawsze wyjscia BT i wejscia MAIN. Praca naprzemienna; brak dwoch masterow. FW pozniej: GPIO26 jako DIN, obsluga BT master RX przy A2DP TX, uzgodnienie formatow i przelaczania. USB BT + 5V_SYS wymaga weryfikacj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
WIDOK OD GORY M1 / ELEMENTY MODULU Antena u gory; USB na dole. J401 lewy, J402 prawy; pin1 przy antenie. Opis spodu odbity LEWO-PRAWO. Dwa wewnetrzne rzedy 1x10. VCC J402.8 -> 5V_SYS (5V, zatwierdzone). Pin 3.3V J401.8 pozostaje NC na M1.
GPIO BT zachowane: TX17/RX16, BCLK18/WS19, DOUT23/DIN26. SD0/SD3 i wszystkie styki niewykorzystywane: NC tylko po stronie bazy. Nie oznacza to braku polaczen Flash wewnatrz modulu. Sprawdzic VCC do VIN regulatora, pull-up RST i tor USB VBUS przed zasileniem.
VoxOne_M1 | FOOTPRINT-2 | A2 | PROTOTYPE / PROVISIONAL
FOOTPRINT-2: 77 footprintow; mapy pin-pad sprawdzone. Moduly: geometria referencyjna PROVISIONAL - NOT FOR MANUFACTURING.
FOOTPRINT-2: RTC pin4=NC. MAIN/BT/DAC: referencje internetowe, rzeczywiste klony wymagaja pomiarow. NIE DO PRODUKCJI.
GND z ARK J101.2
5V po F101 / Q101
Z FB301; to samo zrodlo 5V
I2C PULL-UP: SDA=1-2, SCL=3-4; ON=zworka, OFF=brak. Nadruk PCB: I2C PULL-UP / SDA / SCL / ON/OFF. Pary poprzeczne 1-2 i 3-4; NIE zakladac 1-3 ani 2-4.

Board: 2 copper layers, 81 parts (0 on the bottom side), 56 nets, no tracks yet.

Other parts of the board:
H901, H902, H903, H904: M3 / 3.2mm; MountingHole_3.2mm_M3
